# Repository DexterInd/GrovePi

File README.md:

## **Modular Robotics (Dexter Industries) GrovePi**  

<!-- Remember to add https://mit-license.org/ of our own -->

The GrovePi is an open-source platform for connecting Grove Sensors to the Rasberry Pi. Create IoT (Internet of Things) devices and inventions without the need of soldering! 

Its official API is written in Python, but it can also be interfaced with in other languages such as C, C#, Go and NodeJS. These other variations of the same library came from our contributors.

## Getting Started

In order to quick install the `GrovePi` repository, open up a terminal and type the following command:

```bash
curl -kL dexterindustries.com/update_grovepi | bash
```

The same command can be used for updating the `GrovePi` to the latest version. For more details on how you can install/update your `GrovePi`, please check this [README](Script/README.md).

To install into a virtual environment, first active your virtualenv and type the following command:

```bash
curl -kL dexterindustries.com/update_grovepi | bash -s -- --user-local --bypass-gui-installation
```

To flash the latest firmware to the GrovePi, run
```bash
cd /home/pi/Dexter/GrovePi/Firmware
bash firmware_update.sh
```

Then, import the `grovepi` module and start playing with it. Its documentation can be found [here](https://dexterind.github.io/GrovePi).

The old guide on getting started with the GrovePi can be found [here](http://www.dexterindustries.com/GrovePi/get-started-with-the-grovepi/). It can still prove to be useful if you're unsure how the GrovePi has to be stacked on top of the Raspberry Pi, although it should be pretty obvious.

## Support

### Raspberry Pi Compatibility
The GrovePi is compatible with the Raspberry Pi models A, A+, B, B+, 2, and B3, B3+, A3+, and 4B.

### Documentation
There is [extensive documentation](https://dexterind.github.io/GrovePi) available

### Scratch Support
Once you've done the above command, you can install Scratch support if you want it. This step is optional.
```
sudo bash /home/pi/Dexter/GrovePi/Script/install_scratch.sh
```

If your SD card has Scratch 2.0 installed on it, then this will install GrovePi support for it.
GrovePi integration for Scratch 1.4 is also getting installed.

### Want to use a sensor not in the library yet?  
Ask us in the [forums](http://forum.dexterindustries.com/c/grovepi).  Want to use the GrovePi in a language not currently supported? [Ask and we will help](http://forum.dexterindustries.com/c/grovepi).

### Programming the GrovePi
The GrovePi can be programmed in Python, C, C#, Go, and NodeJS on the Raspberry Pi.  Simply start with one of our [example projects](http://www.dexterindustries.com/GrovePi/projects-for-the-raspberry-pi/) or [example code](https://github.com/DexterInd/GrovePi/tree/master/Software).  
The GrovePi uses an Arduino to interface between the Raspberry Pi and the Grove Sensors, and comes programmed with a standard firmware.  The firmware can be rewritten from the Raspberry Pi.  

### Getting Help
Need help? We [have a forum here where you can ask questions or make suggestions](http://www.dexterindustries.com/GrovePi/projects-for-the-raspberry-pi/).

### Getting Ideas
Need an idea to get started?  [We have a few project examples to get your creative juices flowing](http://www.dexterindustries.com/GrovePi/projects-for-the-raspberry-pi/).

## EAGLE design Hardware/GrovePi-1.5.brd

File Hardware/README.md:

#GrovePi+ 
GrovePi+ is an electronics board designed by Dexter Industries that you can connect to hundreds of different sensors, so you can program them to monitor, control, and automate devices in your life. 

#GrovePi Zero
GrovePi+ is an electronics board designed by Dexter Industries that makes electronics prototyping with the Raspberry Pi Zero easy and fast.  With the GrovePi Zero you can start your connected device projects in minutes.

See more about the GrovePi here:  http://www.dexterindustries.com/grovepi/
Copyright (C) 2016  Dexter Industries 

## License

GNU General Public License v3.0

This program is free software: you can redistribute it and/or modify
it under the terms of the GNU General Public License as published by
the Free Software Foundation, either version 3 of the License, or
(at your option) any later version.

This program is distributed in the hope that it will be useful,
but WITHOUT ANY WARRANTY; without even the implied warranty of
MERCHANTABILITY or FITNESS FOR A PARTICULAR PURPOSE.  See the
GNU General Public License for more details.

You should have received a copy of the GNU General Public License
along with this program.  If not, see <http://www.gnu.org/licenses/>.

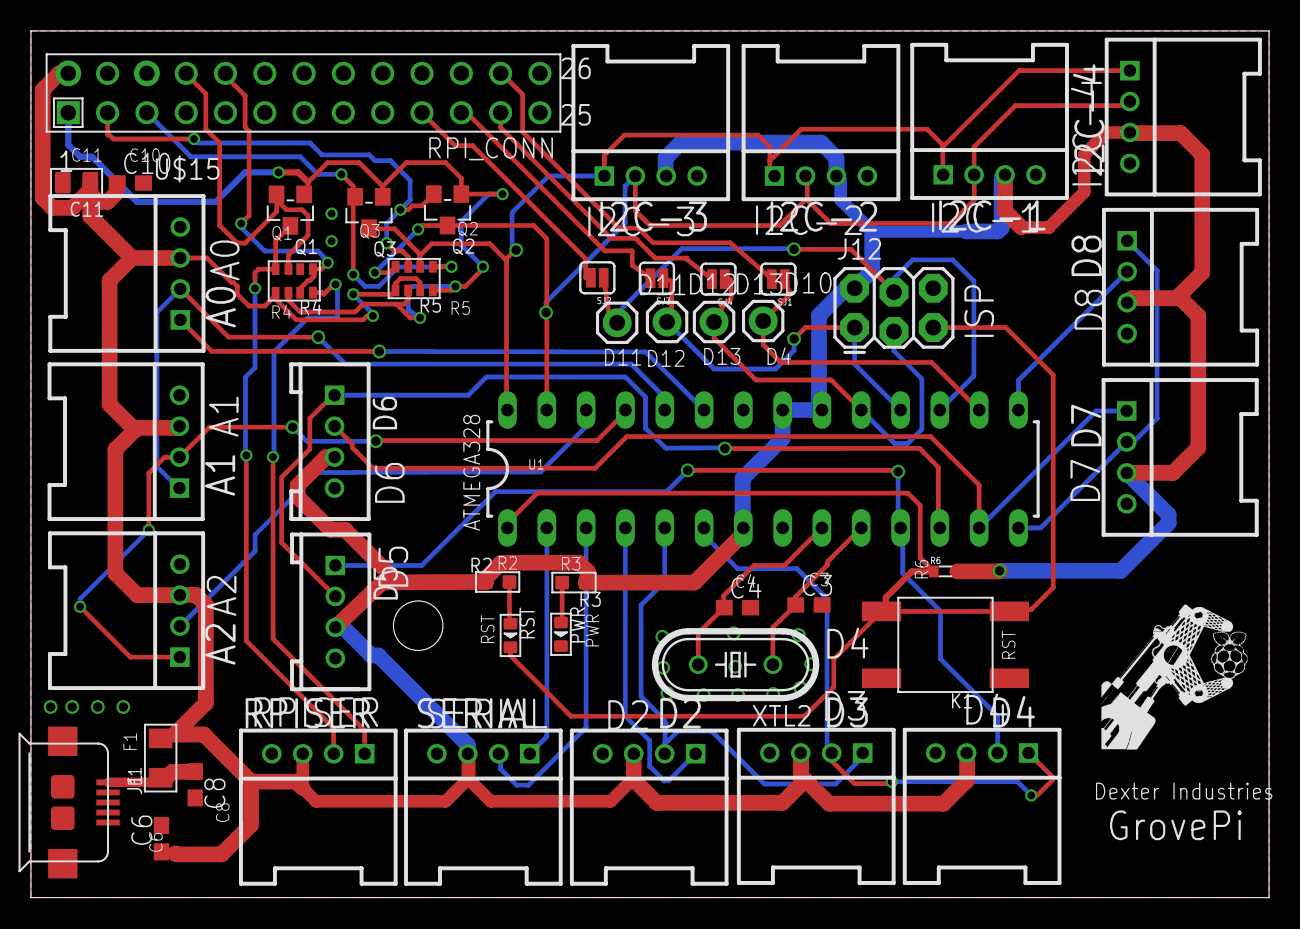
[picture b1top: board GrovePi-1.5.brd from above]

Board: 4 copper layers, 80.0 x 56.0 mm, 47 parts (0 on the bottom side), 39 nets.

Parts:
A0: A0; 4P-2.0-90D
A1: A1; 4P-2.0-90D
A2: A2; 4P-2.0-90D
C3, C4: 22pF; C0603
C6, C8, C10: 0.1uf; C0603
C11: 10uf; C0805
D2: D2; 4P-2.0-90D
D3: D3; 4P-2.0-90D
D4: D4; 4P-2.0-90D
D5: D5; 4P-2.0
D6: D6; 4P-2.0
D7: D7; 4P-2.0-90D
D8: D8; 4P-2.0-90D
D10, D11, D12, D13: M01PTH; 1X01
F1: FUSE-1206; F1206
I2C-1, I2C-2, I2C-3, I2C-4: IIC; 4P-2.0-90D
J1: MICRO-USB-5P-340015001; B-SMD-5P
J12: AVR_SPI_PRG_62X3_LOCK; 2X3_LOCK
K1: BUTTON-4P-3100010P1; 4P-SMD-6.0X6.0X5.0H
PWR: GREEN; LED0603
Q1, Q2, Q3: MOSFET-N-044020001; SOT23
R2, R3: 1k; R0603
R4, R5: 10k; R1206-8
R6: 10k; 0603
RPISER: D0; 4P-2.0-90D
RST: RED; LED0603
SERIAL: D0; 4P-2.0-90D
SJ1, SJ2, SJ3, SJ4: SOLDERJUMPERNC; SJ_2S
U1: ATMEGA328P_PDIP; DIL28-3
U$15: RASPBERRY-PI_REV1
XTL2: HC49/S

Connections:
+3V3: Q1.1, Q2.1, Q3.1, R4.6, R5.6, R5.8, U$15.1
+5V: A0.3, A1.3, A2.3, C6.1, C10.1, C11.1, D2.3, D3.3, D4.3, D5.3, D6.3, D7.3, D8.3, F1.2, I2C-1.3, I2C-2.3, I2C-3.3, I2C-4.3, J12.2, R2.1, R3.1, R4.5, R5.5, R5.7, R6.2, RPISER.3, SERIAL.3, U1.7, U1.20, U1.21, U$15.2
A0: A0.1, U1.23
A1: A0.2, A1.1, U1.24
A2: A1.2, A2.1, U1.25
A3: A2.2, U1.26
D0: SERIAL.1, U1.2
D1: SERIAL.2, U1.3
D2: D2.1, U1.4
D3: D2.2, D3.1, U1.5
D4: D3.2, D4.1, U1.6
D5: D4.2, D5.1, U1.11
D6: D5.2, D6.1, U1.12
D7: D6.2, D7.1, U1.13
D8: D7.2, D8.1, U1.14
D9: D8.2, U1.15
D10: D10.1, SJ1.1, U1.16
GND: A0.4, A1.4, A2.4, C3.2, C4.2, C6.2, C8.2, C10.2, C11.2, D2.4, D3.4, D4.4, D5.4, D6.4, D7.4, D8.4, I2C-1.4, I2C-2.4, I2C-3.4, I2C-4.4, J1.5, J12.6, K1.1, K1.4, PWR.-, R4.2, RPISER.4, SERIAL.4, U1.8, U1.22, U$15.6
MISO1: D12.1, J12.1, SJ3.1, U1.18
MOSI: D11.1, J12.4, SJ2.1, U1.17
unnamed: C4.1, U1.9, XTL2.2
unnamed: PWR.+, R3.2
unnamed: C3.1, U1.10, XTL2.1
unnamed: R2.2, RST.+
RESET: J12.5, K1.2, K1.3, R6.1, RST.-, U1.1
RPI-RX: R4.1, R4.7, U$15.10
RPI-SCL: Q3.2, R5.1, U$15.5
RPI-SDA: Q2.2, R5.3, U$15.3
RPI-TX: Q1.2, R4.3, U$15.8
RPI_MISO: SJ3.2, U$15.21
RPI_MOSI: SJ2.2, U$15.19
RPI_SCL: SJ4.2, U$15.23
RPI_SS: SJ1.2, U$15.24
RX: R4.8, RPISER.1
SCK: D13.1, J12.3, SJ4.1, U1.19
SCL-BOARD: I2C-1.1, I2C-2.1, I2C-3.1, I2C-4.1, Q3.3, R5.2, U1.28
SDA-BOARD: I2C-1.2, I2C-2.2, I2C-3.2, I2C-4.2, Q2.3, R5.4, U1.27
TX: Q1.3, R4.4, RPISER.2
VCC: C8.1, F1.1, J1.1

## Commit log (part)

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2017-05-09 ref #10 : added missing grovepi module's component
2017-05-09 refer #10 : used better words for commenting code
2017-05-19 Embed RCSwitch library to use with 433MHz RF simple link kit
2017-05-22 Revert unwanted changes
2017-05-31 Added dynamic I2C mini motor address support
2017-06-09 Add Grove_OLEDisplay_128*64 Driver
2017-06-12 ref #11 : added dependencies & solved minor issues
2017-06-14 Remove unnecessary files
2017-06-14 Add Grove_OLEDisplay_128*64 Driver and sample (#346)
    * Add Grove_OLEDisplay_128*64 Driver
    * Remove unnecessary files
    * Change License
2017-06-15 Cleaned code up, fixed issue with ReadDHT
    Changed b := []byte{CommandDHTRead, pin, 1, 0} to b := []byte{CommandDHTRead, pin, 0, 0}
    Code was refactored by @adzeitor
2017-06-16 Cleaned code up, fixed issue with ReadDHT (#351)
    Changed b := []byte{CommandDHTRead, pin, 1, 0} to b := []byte{CommandDHTRead, pin, 0, 0}
    Code was refactored by @adzeitor
2017-06-23 ref #10 : added description on how to wire the hardware
2017-06-26 Uodated led example
2017-06-27 Updated library (#354)
2017-06-27 hotfix for DHT's bad sensor readings (#337)
    * ref #10 : switched mother branch -> implemented filtering algo for DHT
    * also added the new packages to be installed in the install.sh script
    * no tests ran yet
    * ref #10 : solved errors & tested the code
    * ref #10 : added code comments
    * ref #10 : added more locks
2017-06-28 Added support for Grove Temperature & Humidity Sensor (SHT31)
2017-06-30 corrected errors in the readme tutorial + constructor improve for the [high temperature sensor] (#357)
    * ref #11 , ref #8 : solved bad readings for the high temperature sensor
    * ref #11 : added dependencies & solved minor issues
    * ref #11 : added README, calibrated sensor & solved indentention
    * ref #11 : updated README
    * ref #11 : updated README
    * ref #11 : solved typo in calibration tutorial
2017-07-05 timing issue [i2c sunlight] sensor (#358)
    * ref #11 , ref #8 : solved bad readings for the high temperature sensor
    * ref #11 : added dependencies & solved minor issues
    * ref #11 : added README, calibrated sensor & solved indentention
    * ref #11 : updated README
    * ref #11 : updated README
    * ref #11 : solved typo in calibration tutorial
2017-07-17 ref #16 : added RST long package description
2017-07-17 ref #16 : corrected typo and added keywords for the package
2017-07-22 Removed duplicate README.md
2017-07-23 Added DigitalButton, RotaryAngleAnalogSensor and LoudnessAnalogSensor implementations (#361)
    * Added DigitalButton, RotaryAngleAnalogSensor and LoudnessAnalogSensor implementations. Updated tests and README
    * Removed duplicate README.md
    * Re-added instructions to install Node.js
2017-07-25 'var' added on dustDigitalSensor
2017-07-30 Deleted class who was never used and was not backward compatible
2017-07-30 Merges + bumped NPM version (#366)
    * Updated for I2C and Functionality
    I think there's still an I2C arbitration bug in this code in the setText function but it seems to work most of the time. I believe it's related to the I2C arbitration but am not sure as the error is 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
    * New File to Manage the Grove LCD RGB Display
    New addition to manage the Grove LCD display...there is a bug with the setText and the I2C arbitration but mostly works as expected. I am not sure what I am missing here but advice is appreciated.
    * Update package.json
2017-08-02 removing the flicker from [Home_Weather_Display] project (#367)
    * ref #11 , ref #8 : solved bad readings for the high temperature sensor
    * ref #11 : added dependencies & solved minor issues
    * ref #11 : added README, calibrated sensor & solved indentention
    * ref #11 : updated README
    * ref #11 : updated README
    * ref #11 : solved typo in calibration tutorial
2017-08-13 fixes lcd screen from blinking when quickly refreshed
    Changes Scratch file to reference setText_norefresh function instead of setText
2017-08-29 removed unnecessary grove_rgb_lcd file from project
2017-09-09 ref RobertLucian/GrovePi#17 : hotfix - added exception handler
2017-09-13 Whoops forgot version check
    Forgot the version check.
2017-09-19 Fixed Node-crashing TypeError; typos; camelCase
    # TypeError
    When running this as a dependency with the GrovePi, Node consistently crashed with the following message:
    `
    /home/pi/.../node_modules/node-grovepi/sensors/digitalButton.js:27
    var milliseconds = currentDateTime.getTime() - pressedDateTime.getTime()
    { imagine an arrow pointing up at the dot "." in "pressedDateTime.getTime() }
2017-09-19 incremented version
2017-09-26 Skipping SSL checks on install command in README
2017-09-27 Update README.md
    The truth is revealed.
2017-10-09 ref RobertLucian/GrovePi#19 : feature - fixed typos
2017-11-16 Typo error in grove_light_sensor.py (#382)
    Thanks @yannick-mayeur for the contribution!
2017-12-18 Minor Change To README
2018-02-15 Add Ruby support
2018-02-21 Get rid of redundant functions
2018-02-22 Add Ruby support (#388)
    * Add Ruby support
    * Get rid of redundant functions
    * Fix README.md
2018-03-20 tested version
2018-03-20 change Package name
2018-03-20 line Unix LF
2018-03-22 1st public release
2018-03-26 Removing some unrelated files
2018-03-27 Integrate Scratch 1.4 and Scratch 2 support on standalone Raspbian
2018-03-27 fix to try
2018-03-28 added some more documenation
    incl. Screenshots of a simple Flow
2018-04-13 add a new Flogo.io Activity for DigitalWrite with fixed GOlang Package, too (#393)
    * tested version
    * first draft
    * update
    * actual path
    * change Package name
    * new
2018-04-23 feature - use setup.py to install the package & trim-down scripts
2018-04-23 feature - change script_tools url for testing purposes
2018-04-23 feature - more granular control over the installation phase
2018-04-24 feature - add in another option for install script
2018-04-24 feature - add feedback output and cut script_tools' output
2018-04-24 feature - update the root README
2018-04-24 feature - fix console feedback issue
2018-04-24 feature - fix parser issue with script_tools
2018-04-24 feature - removing duplicate code
2018-04-24 feature - missing extension on script and restoring real url address
2018-04-30 feature - add a few missing packages with apt-get
2018-04-30 feature - make path more readable
2018-04-30 feature - don't build packages and instead, rely on apt-get
2018-05-03 feature - put everything in functions
2018-05-03 feature - add comment on a needed basis
2018-05-03 feature - use quiet mode on the GrovePi text-logo
2018-05-03 feature - removing some echoes and moving a variable
2018-05-03 feature - add an echo in here and remove another one
2018-05-04 feature - check if script is run with pi user
2018-05-08 feature - fix global variable issue
2018-05-10 feature - change grovepi install script to accommodate rfr tools
2018-05-10 feature - change how we do the installation (#398)
    * feature - change grovepi install script to accommodate rfr tools
    * feature - adjust readme accordingly
    * feature - add condition to if statement
2018-05-16 adjust Doc ref Path
    without this adjustment the Implementation get's automatically pulled for my GitHub location, regardless what is entered into Flogo.
2018-05-17 feature - change install script sources (#400)
    * feature - change grovepi install script to accommodate rfr tools
    * feature - adjust readme accordingly
    * feature - add condition to if statement
    * feature - change sources
2018-05-23 feature - change script_tools reference
2018-05-24 Reorg install_scratch.sh so that it supports the up to date scripts
2018-06-05 fix - make avr programmer work in pio environment
2018-06-05 hotfix - install script_tools before rfr_tools (#404)
2018-06-05 Revert "hotfix - install script_tools before rfr_tools (#404)" (#405)
    This reverts commit 880a478d311b89173c818d275a02c34e40bb7b14.
2018-06-29 hotfix - added subpackages & ignored examples/READMEs
2018-06-30 hotfix - import packages in example scripts the right way
2018-07-03 fix - add 4 methods back in
2018-07-05 fix - remove unnecessary digitalWrites and relocate code
2018-07-09 fix - major speed/reliability improvements
2018-07-10 fix - improve the acquisition rate for the US sensor (+ when it's not there)
2018-07-11 fix - making the rest of functions work with the new fw + add ir support
2018-07-20 fix - small change to one of the grovepi functions
2018-07-23 fix - the IR receiver and slightly change the api
2018-07-26 hotfix - add int casting for python 3 & slightly change the README (#420)
2018-07-27 hotfix - change the README a bit (#422)
    * hotfix - change the README a bit
    * hotfix - fixing grammatical error
2018-07-27 fix - make the Encoder library prettier
2018-07-31 fix - adding more to the documentation
2018-08-01 fix - reorganize the firmware directory
2018-08-02 fix - add the built documentation
2018-08-02 fix - change website url to the designated one for dexterind
2018-08-07 hotfix - provide option to install a minimal version of the GrovePi
2018-08-08 fix - add a list to hold all the versions of the firmware that the current library works with
2018-08-09 fix - change the documentation slightly
2018-08-14 hotfix - update README for install script
2018-08-14 hotfix - also check if script_tools got installed as a dependency
2018-08-14 hotfix - dummy change to see if Nicole still hears noise
2018-08-15 Added docstring to create_char
2018-08-17 hotfix - change exit codes
2018-08-20 Python3 support
2018-08-21 hotfix - remove the submodules for a very old version of the fw
2018-08-21 hotfix - add a hyperlink for the GPS & add article on serial ports
2018-08-23 hotfix - reorganize python directory
2018-08-24 hotfix - add test for source imports
2018-08-24 hotfix - use the correct paths for the test suite
2018-08-27 hotfix - requirements file, README & setup
2018-08-27 hotfix - update version & change pypi description
2018-08-30 hotfix - adapt setup.py to all sublibraries w/o changing a bit
2018-08-30 hotfix - change the README to be more accurate
2018-08-31 Revert "hotfix - getting rid of the old files"
    This reverts commit dc25ac96c2a27f3c89dfb9515732b3a7f9d292ac.
2018-08-31 hotfix - fix the problem with the license
2018-09-12 hotfix - add paths example projects (#432)
    * hotfix - bring changes to the python directory
    * hotfix - adapt setup.py to all sublibraries w/o changing a bit
    * hotfix - fix problems with setup.py
    * hotfix - change readme and remove some things unnecessary
    * hotfix - change the README to be more accurate
    * hotfix - add 2-liner to the license on the root dir
2018-09-12 hotfix - update required packages
2018-09-21 fix - the DHT sensors
2018-12-12 hotfix - use spaces instead of tabs (#434)
2019-02-14 Revert "fix - temporary change to the source repository of the GrovePi"
    This reverts commit 55e09e6940b3ea6f204eea203f6a08f955fe9938.
2019-02-14 change phrasing
2019-02-14 re-update the docs folder for mkdocs
2019-04-19 add functions for setting/unsetting/monitoring the interrupts on pins
2019-04-23 fix bugs w/ the firmware
2019-04-25 support for any number of isrs & support dust & encoders
2019-04-25 add rough API in the docs for the new set/unset/read interrupt-based methods
2019-04-27 adding more to the documentation
2019-04-30 Update json package
    This should solve the security alert, do we want to risk breaking it without testing?
2019-05-04 Replaced deprecated dustSensorRead()
    The dustSensorRead() method in grovepi.py is deprecated, thus the example script will not execute. This example works again if the name is changed to 'dust_sensor_read()'.
2019-05-19 Update README.md
    an d -> and
2019-05-24 Replace Buffer to Buffer.alloc and Buffer.from to avoir deprecation https://nodejs.org/en/docs/guides/buffer-constructor-deprecation/
2019-05-29 Replace Buffer to Buffer.alloc and Buffer.from to avoir deprecation h… (#452)
    * Replace Buffer to Buffer.alloc and Buffer.from to avoir deprecation https://nodejs.org/en/docs/guides/buffer-constructor-deprecation/
    * Correct bug on DigitalInput Sensor read. Read 2 bytes instead of one to get the digital value. Don't know own it could work before... Tested with GrovePi firmware 1.3.0.
2019-09-05 Firmware Commenting Code
    Commenting some firmware code.
2019-11-12 add info about compatibility with Raspberry PI
2020-01-16 bring multi grovepi up to firmware 1.4
2020-01-16 add comments; fix addr in 2 files
2020-02-18 Change company name in readme
2020-03-03 add virtualenv command
2020-04-01 curses seem to be missing
2020-05-19 Add keyboard interrupt handling in low level i2c read/write
2020-09-21 fix broken link
    old link:
    http://www.seeedstudio.com/wiki/Grove_-_Temperature_and_Humidity_Sensor_Pro
    new link:
    http://www.seeedstudio.com/wiki/Grove-Temperature_and_Humidity_Sensor_Pro
2020-10-17 fix troubleshooting i2ctest
2021-02-15 Update README.md
    Add link to documentation
2021-03-30 backup
2021-04-12 Removed Deprecated NodeJS Buffertools Module

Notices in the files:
parts and their libraries:
SparkFun-DigitalIC: Licensing: CC v3.0 Share-Alike You are welcome to use this library for commercial purposes.
